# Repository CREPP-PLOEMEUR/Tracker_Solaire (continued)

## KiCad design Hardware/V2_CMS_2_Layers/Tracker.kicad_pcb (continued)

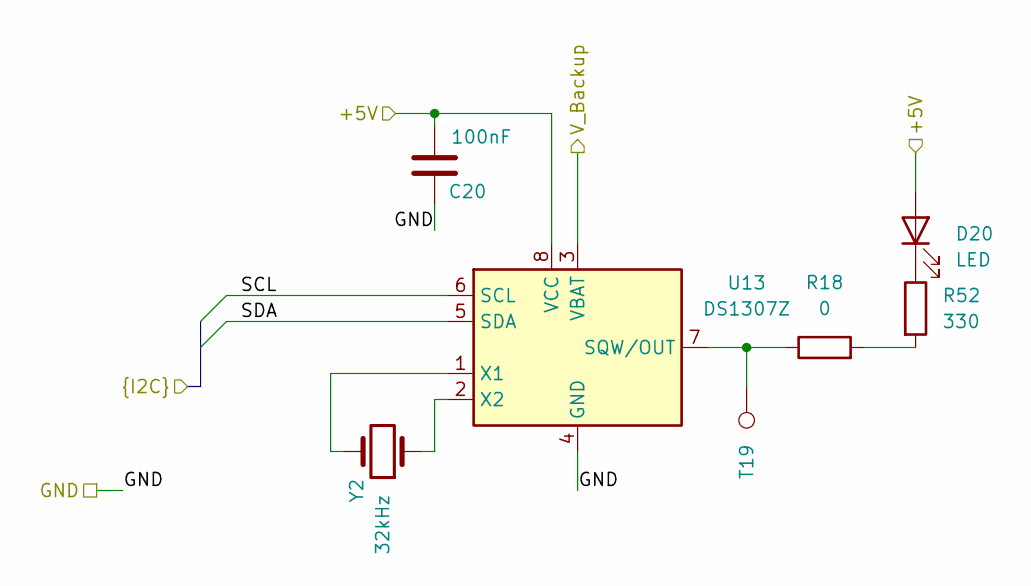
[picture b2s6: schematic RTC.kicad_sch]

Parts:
C20: 100nF; C_0603_1608Metric
D20: LED; LED_0603_1608Metric
R18: 0; R_0603_1608Metric
R52: 330; R_0603_1608Metric
T19: TP; TestPoint_Pad_D1.0mm
U13: DS1307Z; SO-8_5.3x6.2mm_P1.27mm
Y2: 32kHz; Crystal_SMD_3215-2Pin_3.2x1.5mm

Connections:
+VCap: U13.3 (VBAT); also elsewhere on the board
/Anemometer/SCL: U13.6 (SCL); also elsewhere on the board
unnamed: D20.1 (K), R52.1
unnamed: R18.2, R52.2
unnamed: R18.1, T19.1, U13.7 (SQW/OUT)
unnamed: U13.1 (X1), Y2.2
unnamed: U13.2 (X2), Y2.1

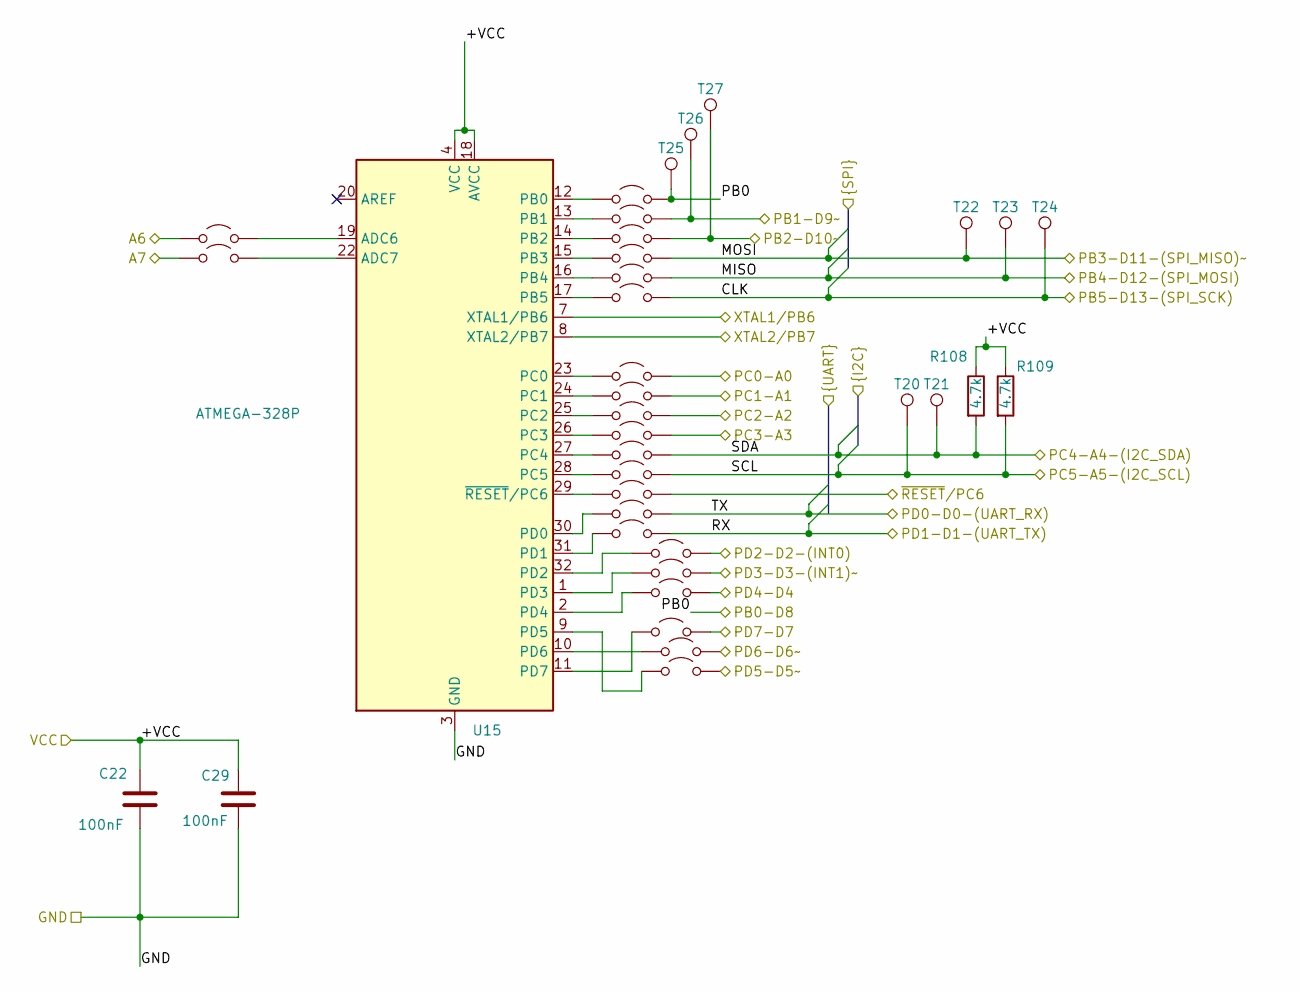
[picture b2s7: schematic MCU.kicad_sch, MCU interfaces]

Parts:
C22, C29: 100nF; C_0603_1608Metric
JP1, JP2, JP3, JP9, JP10, JP11, JP12, JP13, JP14, JP15, JP16, JP17, JP18, JP19, JP20, JP21, JP22, JP23, JP24, JP25, JP26, JP27, JP28: Jumper_2_Open; PinHeader_1x02_P1.27mm_Vertical
R108, R109: 4.7k; R_0603_1608Metric
T20, T21, T22, T23, T24, T25, T26, T27: TP; TestPoint_Pad_D1.0mm
U15: ATMEGA-328P; TQFP-32_7x7mm_P0.8mm

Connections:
/Anemometer/SCL: JP19.2 (B), R109.2, T20.1; also elsewhere on the board
/DTR: JP20.2 (B); also elsewhere on the board
/GNSS_RX: JP27.2 (B); also elsewhere on the board
/GNSS_TX: JP26.2 (B); also elsewhere on the board
/MCU/A6: JP1.2 (B); also elsewhere on the board
/MCU/A7: JP3.2 (B); also elsewhere on the board
/MCU/CLK: JP13.2 (B), T24.1; also elsewhere on the board
/MCU/MISO: JP12.2 (B), T23.1; also elsewhere on the board
/MCU/MOSI: JP11.2 (B), T22.1; also elsewhere on the board
/MCU/PB0: JP2.2 (B), T25.1; also elsewhere on the board
/MCU/PB1-D9~: JP9.2 (B), T26.1; also elsewhere on the board
/MCU/PB2-D10~: JP10.2 (B), T27.1; also elsewhere on the board
/MCU/PC0-A0: JP14.2 (B); also elsewhere on the board
/MCU/PC2-A2: JP16.2 (B); also elsewhere on the board
/MCU/PC3-A3: JP17.2 (B); also elsewhere on the board
/MCU/PD3-D3-(INT1)~: JP24.2 (B); also elsewhere on the board
/MCU/PD4-D4: JP25.2 (B); also elsewhere on the board
/MCU/PD5-D5~: JP28.2 (B); also elsewhere on the board
/MCU/RX: JP22.2 (B); also elsewhere on the board
/MCU/TX: JP21.2 (B); also elsewhere on the board
/WIND_INTERRUPT: JP23.2 (B); also elsewhere on the board
unnamed: JP1.1 (A), U15.19 (ADC6)
unnamed: JP2.1 (A), U15.12 (PB0)
unnamed: JP3.1 (A), U15.22 (ADC7)
unnamed: JP9.1 (A), U15.13 (PB1)
unnamed: JP10.1 (A), U15.14 (PB2)
unnamed: JP11.1 (A), U15.15 (PB3)
unnamed: JP12.1 (A), U15.16 (PB4)
unnamed: JP13.1 (A), U15.17 (PB5)
unnamed: JP14.1 (A), U15.23 (PC0)
unnamed: JP15.1 (A), U15.24 (PC1)
unnamed: JP16.1 (A), U15.25 (PC2)
unnamed: JP17.1 (A), U15.26 (PC3)
unnamed: JP18.1 (A), U15.27 (PC4)
unnamed: JP19.1 (A), U15.28 (PC5)
unnamed: JP20.1 (A), U15.29 (~RESET/PC6)
unnamed: JP21.1 (A), U15.30 (PD0)
unnamed: JP22.1 (A), U15.31 (PD1)
unnamed: JP23.1 (A), U15.32 (PD2)
unnamed: JP24.1 (A), U15.1 (PD3)
unnamed: JP25.1 (A), U15.2 (PD4)
unnamed: JP26.1 (A), U15.11 (PD7)
unnamed: JP27.1 (A), U15.10 (PD6)
unnamed: JP28.1 (A), U15.9 (PD5)

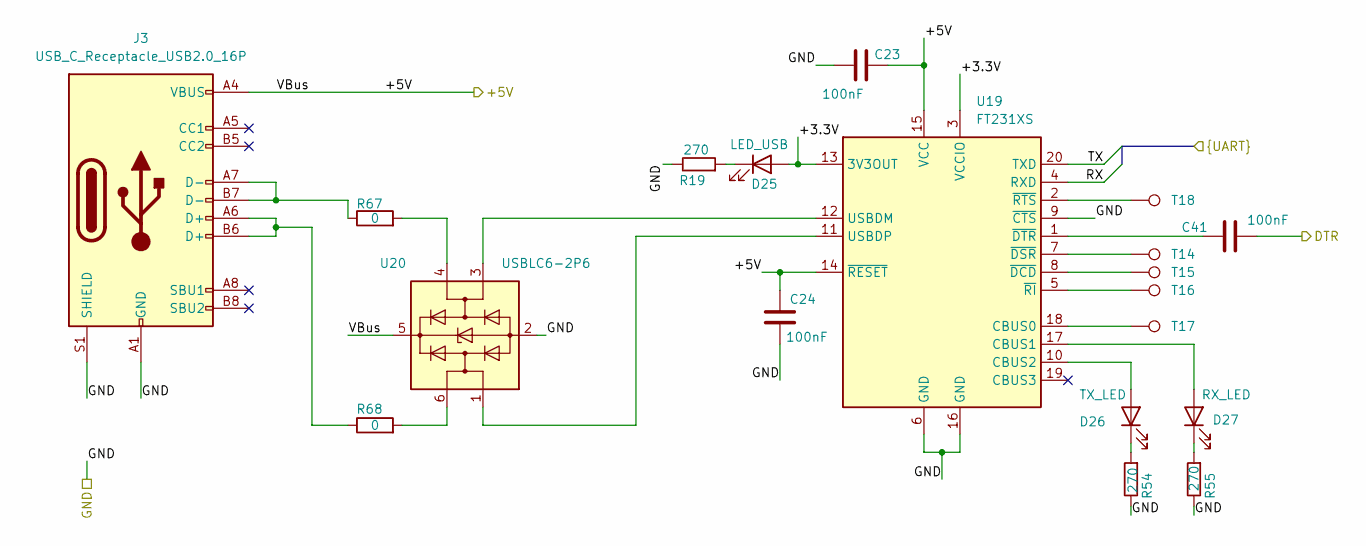
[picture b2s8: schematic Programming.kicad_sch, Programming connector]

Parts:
C23, C24, C41: 100nF; C_0603_1608Metric
D25: LED_USB; LED_0603_1608Metric
D26: TX_LED; LED_0603_1608Metric
D27: RX_LED; LED_0603_1608Metric
J3: USB_C_Receptacle_USB2.0_16P; USB_C_Receptacle_GCT_USB4085
R19, R54, R55: 270; R_0603_1608Metric
R67, R68: 0; R_0603_1608Metric
T14, T15, T16, T17, T18: TP; TestPoint_Pad_D1.0mm
U19: FT231XS; SSOP-20_3.9x8.7mm_P0.635mm
U20: USBLC6-2P6; SOT-666

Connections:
/DTR: C41.2; also elsewhere on the board
/MCU/RX: U19.4 (RXD); also elsewhere on the board
/MCU/TX: U19.20 (TXD); also elsewhere on the board
/Programming/+3.3V: D25.2 (A), U19.3 (VCCIO), U19.13 (3V3OUT)
unnamed: D25.1 (K), R19.1
unnamed: D26.2 (A), U19.10 (CBUS2)
unnamed: D26.1 (K), R54.1
unnamed: D27.2 (A), U19.17 (CBUS1)
unnamed: D27.1 (K), R55.1
unnamed: J3.A6 (D+), J3.B6 (D+), R68.1
unnamed: J3.A7 (D-), J3.B7 (D-), R67.1
unnamed: R67.2, U20.4 (I/O2)
unnamed: R68.2, U20.6 (I/O1)
unnamed: T17.1, U19.18 (CBUS0)
unnamed: U19.12 (USBDM), U20.3 (I/O2)
unnamed: U19.11 (USBDP), U20.1 (I/O1)
unnamed: T15.1, U19.8 (~DCD)
unnamed: T14.1, U19.7 (~DSR)
unnamed: C41.1, U19.1 (~DTR)
unnamed: T16.1, U19.5 (~RI)
unnamed: T18.1, U19.2 (~RTS)

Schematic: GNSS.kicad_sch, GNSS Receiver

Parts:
AE1: Internal_antenna; MountingHole_2.2mm_M2_DIN965_Pad
C7, C36: 100nF; C_0603_1608Metric
C9, C10, C34: 120pF; C_0603_1608Metric
C25, C26: 330pF; C_0603_1608Metric
C35: 1nF; C_0603_1608Metric
D2: POS_ENABLE; LED_0603_1608Metric
D24: GNSS_USB; LED_0603_1608Metric
D28: LED_EXT_ANTENNA; LED_0603_1608Metric
D34: GNSS_BATT; LED_0603_1608Metric
D36: 1N4148; D_SOD-323
J5: USB_C_Receptacle_USB2.0_16P; USB_C_Receptacle_GCT_USB4085
J10: 132415; SMA_Molex_73251-1153_EdgeMount_Horizontal
L6: 56nH; L_0603_1608Metric
L9: 39nH; L_0603_1608Metric
Q1: SI2302; SOT-23
Q10: CJ3401; SOT-23
Q11: 2N7002; SOT-23
R11, R12, R15, R69, R70, R71, R72, R94, R106, R107: 0; R_0603_1608Metric
R13, R14, R58: 1k; R_0603_1608Metric
R16, R73, R74, R95: 330; R_0603_1608Metric
R17: R_680K_SMD_0603; R_0603_1608Metric
R56: 100k; R_0603_1608Metric
R57: 10k; R_0603_1608Metric
R92: R_100K_SMD_0603; R_0603_1608Metric
R93: R_1K_SMD_0603; R_0603_1608Metric
T1, T4, T5, T7, T8, T33, T34, T38, T40, T52: TP; TestPoint_Pad_D1.0mm
U3: NEO-M8M; ublox_NEO
U21: AS193-73LF; SOT-23-6
U26: USBLC6-2P6; SOT-666
U27: LP2985-3.3; SOT-23-5

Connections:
+VCap_GNSS: U3.22 (V_BCKP); also elsewhere on the board
/GNSS/D+: U3.6 (USB_DP), U26.3 (I/O2)
/GNSS/D-: U3.5 (USB_DM), U26.1 (I/O1)
/GNSS/VBus: J5.A4 (VBUS), J5.A9 (VBUS), J5.B4 (VBUS), J5.B9 (VBUS), R71.1, U26.5 (VBUS)
/GNSS/VCC_RF: L9.2, R17.2, U3.9 (VCC_RF)
/GNSS/VCC_USB: C36.1, D36.2 (A), R72.2, U3.7 (VDD_USB), U27.5 (VOUT)
/GNSS/~ANTENNA_DETECT: C26.1, L6.1, Q1.1 (G), R17.1, R57.2, T52.1, U21.6 (V1)
/GNSS_ENABLED: R107.2; also elsewhere on the board
/GNSS_RX: R12.1; also elsewhere on the board
/GNSS_TX: R11.1; also elsewhere on the board
unnamed: AE1.1 (A), C10.2
unnamed: C25.2, L6.2, R56.2
unnamed: D2.2 (A), R16.1
unnamed: D24.2 (A), R73.1
unnamed: D28.1 (K), R74.2
unnamed: D34.2 (A), R95.1
unnamed: D36.1 (K), Q11.1 (G), R92.2, R107.1
unnamed: J5.A6 (D+), J5.B6 (D+), R69.1
unnamed: J5.A7 (D-), J5.B7 (D-), R70.1
unnamed: C34.2, J10.1 (In), L9.1, R56.1
unnamed: Q1.2 (S), R58.2, R106.2, T1.1, U21.4 (V2)
unnamed: Q10.3 (D), R94.2, T40.1, U3.23 (VCC)
unnamed: Q10.1 (G), Q11.3 (D), R93.1
unnamed: R12.2, R13.1
unnamed: R15.1, R16.2
unnamed: R69.2, U26.4 (I/O2)
unnamed: R70.2, U26.6 (I/O1)
unnamed: R72.1, R73.2
unnamed: R94.1, R95.2
unnamed: R74.1, R106.1
unnamed: T38.1, U3.2 (D_SEL)
unnamed: T8.1, U3.4 (EXTINT)
unnamed: C9.2, U3.11 (RF_IN)
unnamed: R13.2, R14.2, T4.1, U3.21 (RXD/SPI_MOSI)
unnamed: T34.1, U3.19 (SCL/SPI_CLK)
unnamed: T33.1, U3.18 (SDA/~SPI_CS)
unnamed: R15.2, U3.3 (TIMEPULSE)
unnamed: R11.2, T5.1, U3.20 (TXD/SPI_MISO)
unnamed: T7.1, U3.1 (~SAFEBOOT)
unnamed: C9.1, U21.5 (J1)
unnamed: C10.1, U21.1 (J2)
unnamed: C34.1, U21.3 (J3)
unnamed: C35.1, U27.4 (BP)
unnamed: R71.2, U27.1 (VIN), U27.3 (ON/~OFF)

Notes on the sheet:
V_{RX}=5*${a52a78e2-18e3-4ec6-8d46-591b24bd5bd1:VALUE}/(${a52a78e2-18e3-4ec6-8d46-591b24bd5bd1:VALUE}+${f5d83104-4b79-4b80-ade9-bfd7c6659042:VALUE})
EXT_ANTENNA

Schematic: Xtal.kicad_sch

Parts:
C7, C8: 22pF; C_Disc_D4.7mm_W2.5mm_P5.00mm
Y1: 16MHz; Crystal_HC49-4H_Vertical

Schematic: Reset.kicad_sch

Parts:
J11: KF128-2.54_2P; TerminalBlock_Phoenix_MPT-0,5-2-2.54_1x02_P2.54mm_Horizontal
R46: 10k; R_0603_1608Metric
SW4: PB_SMD_12V_50MA_6MM_6MM; SW_Push_1P1T_NO_CK_KSC7xxJ

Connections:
/DTR: J11.2, R46.2, SW4.2 (B); also elsewhere on the board

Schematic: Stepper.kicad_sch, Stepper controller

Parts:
C30: 100nF; C_0603_1608Metric
C31, C32: XX; C_0603_1608Metric
D22, D35: 1N4148; D_SOD-323
IC1: L6208; ST_PowerSSO-36_SlugDown_ThermalVias
J16: Stepper; PhoenixContact_MSTBA_2,5_4-G-5,08_1x04_P5.08mm_Horizontal
J22: KF128-2.54_2P; TerminalBlock_Phoenix_MPT-0,5-2-2.54_1x02_P2.54mm_Horizontal
J26: +24V; PhoenixContact_MSTBA_2,5_2-G-5,08_1x02_P5.08mm_Horizontal
J31: Motor_Control_Pull_Up; TerminalBlock_Phoenix_MPT-0,5-3-2.54_1x03_P2.54mm_Horizontal
J32: KF128-2.54_3P; TerminalBlock_Phoenix_MPT-0,5-3-2.54_1x03_P2.54mm_Horizontal
R64, R97, R99, R101: 10k; R_0603_1608Metric
R65, R66: XX; R_0603_1608Metric
R79, R80: 0.33; R_Axial_DIN0414_L11.9mm_D4.5mm_P15.24mm_Horizontal
R84, R85, R86, R87, R88, R89: 220; R_0603_1608Metric
R98, R100: 10k; R_0603_1608Metric; not fitted
R103: 0; R_0603_1608Metric
RV2: Vref_B; Potentiometer_Bourns_3314S_Horizontal
RV3: Vref_A; Potentiometer_Bourns_3314S_Horizontal
T3, T28, T29, T30, T31, T32, T42: TP; TestPoint_Pad_D1.0mm
U23, U24, U25: PC817XI; SOP-4_4.4x2.6mm_P1.27mm

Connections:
+24V: D35.2 (A), IC1.17 (VS_B), IC1.20 (VS_A), J26.2; also elsewhere on the board
/MCU/A7: J22.2, R64.2; also elsewhere on the board
/MCU/PB0: U24.2; also elsewhere on the board
/MCU/PB1-D9~: U25.2; also elsewhere on the board
/MCU/PB2-D10~: U23.2; also elsewhere on the board
/Stepper/CONTROL: IC1.13 (CONTROL), R97.2, R98.1, T42.1
/Stepper/HALF/FULL: IC1.12 (HALF/FULL), R99.2, R100.1, T3.1
/Stepper/RC_1: C31.1, IC1.4 (RCA), R65.2, T28.1
/Stepper/RC_2: C32.1, IC1.9 (RCB), R66.2, T29.1
/Stepper/SENSE_A: IC1.3 (SENSE_A), R80.1
/Stepper/SENSE_B: IC1.10 (SENSE_B), R79.1
/Stepper/STEP_CW: IC1.2 (CW/CWW), J32.1, R88.2, T31.1, U24.4
/Stepper/STEP_ENABLE: IC1.14 (EN), J32.2, R87.2, T32.1, U25.4
/Stepper/STEP_PULSE: IC1.1 (CLOCK), J32.3, R89.2, T30.1, U23.4
/Stepper/Vref_A: IC1.24 (VREF_A), RV3.2
/Stepper/Vref_B: IC1.11 (VREF_B), RV2.2
unnamed: C30.2, R101.2
unnamed: C30.1, D22.2 (A), D35.1 (K)
unnamed: D22.1 (K), IC1.15 (VBOOT)
unnamed: IC1.5 (OUT1A), J16.1
unnamed: IC1.8 (OUT1B), J16.3
unnamed: IC1.21 (OUT2A), J16.2
unnamed: IC1.16 (OUT2B), J16.4
unnamed: IC1.22 (VCP), R101.1
unnamed: R84.1, U23.1
unnamed: R85.1, U24.1
unnamed: R86.1, U25.1
unnamed: R64.1, R103.1

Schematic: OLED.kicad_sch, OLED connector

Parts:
J8: I2C_Selector; PinHeader_2x03_P2.54mm_Vertical
J9: OLED_SOCKET; PinSocket_1x04_P2.54mm_Vertical

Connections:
/Anemometer/SCL: J8.5, J8.6; also elsewhere on the board
/OLED/A: J8.4, J9.1
/OLED/B: J8.3, J9.2

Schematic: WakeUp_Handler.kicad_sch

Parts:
D30, D32: 1N4148; D_SOD-323
J35, J36: KF128-2.54_2P; TerminalBlock_Phoenix_MPT-0,5-2-2.54_1x02_P2.54mm_Horizontal
Q9: 2N7002; SOT-23
R75, R76, R81, R82, R83: 10k; R_0603_1608Metric
RV1: Light_Reference; Potentiometer_Bourns_3314S_Horizontal
SW7: PB_SMD_12V_50MA_6MM_6MM; SW_Push_1P1T_NO_CK_KSC7xxJ
T35, T36, T44, T50, T51: TP; TestPoint_Pad_D1.0mm
U29: LM358DR; TSSOP-8_4.4x3mm_P0.65mm

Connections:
/Power_Supply/WakeUp_Handler/PS_CTRL: Q9.3 (D), R76.1, T36.1; also elsewhere on the board
/Power_Supply/WakeUp_Handler/WIND_INTERRUPT: D30.2 (A); also elsewhere on the board
unnamed: D30.1 (K), D32.1 (K), Q9.1 (G), R82.2, R83.2, T50.1, U29.1
unnamed: D32.2 (A), J36.2, SW7.1 (A), T51.1
unnamed: J35.1, R75.2, R81.1, T35.1
unnamed: R81.2, R82.1, U29.3 (+)
unnamed: RV1.2, T44.1, U29.2 (-)

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
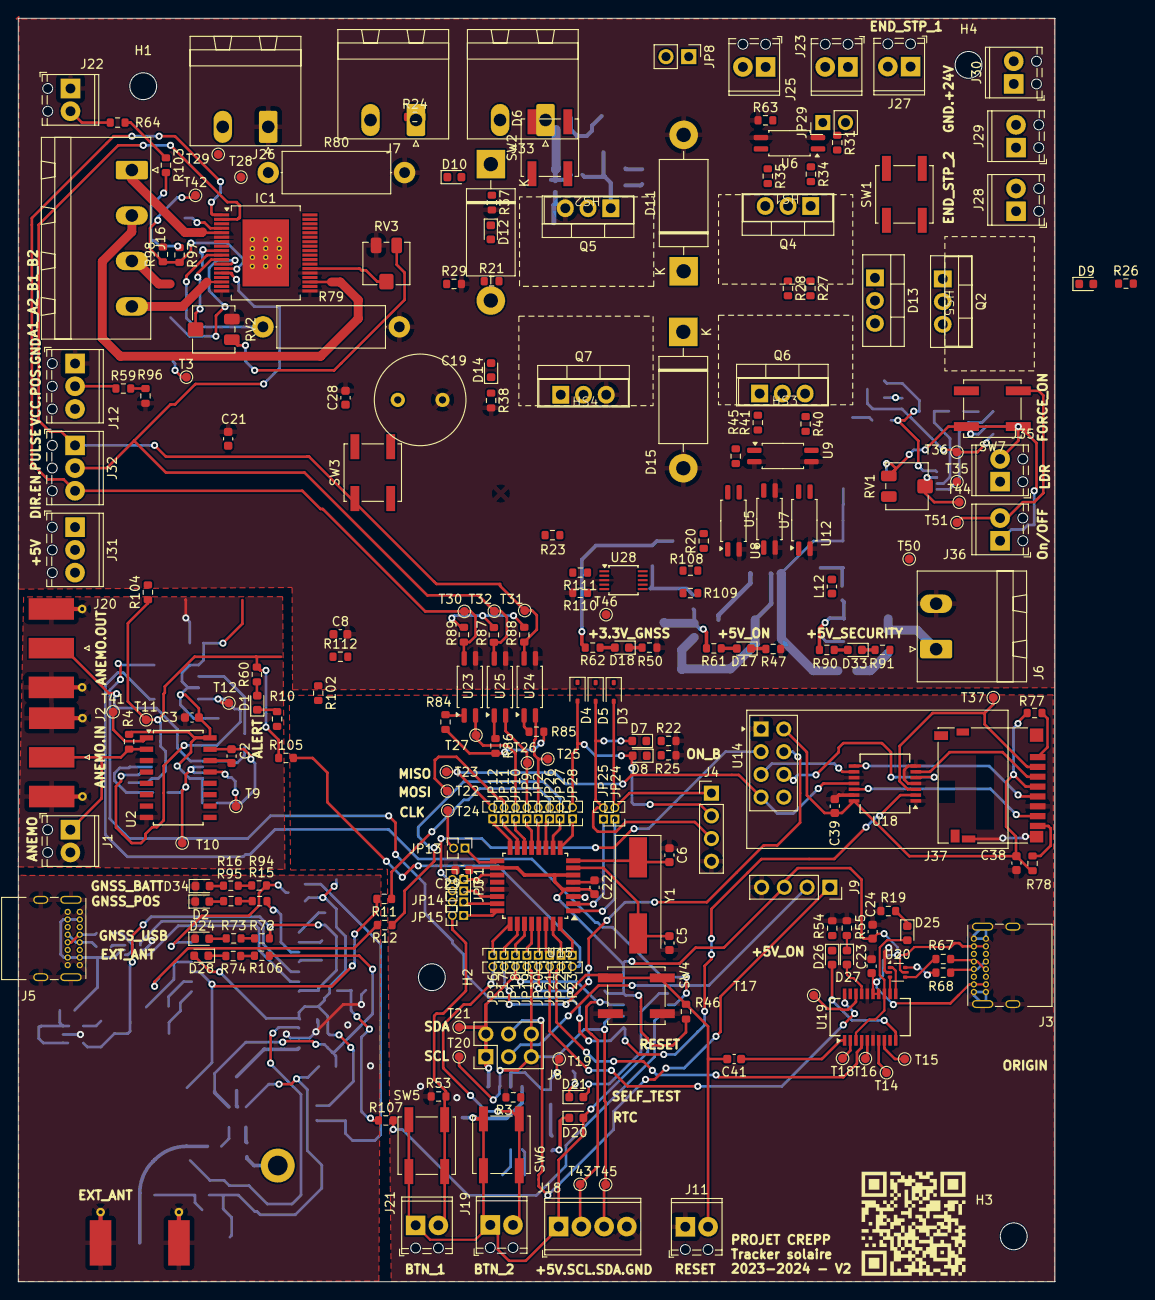
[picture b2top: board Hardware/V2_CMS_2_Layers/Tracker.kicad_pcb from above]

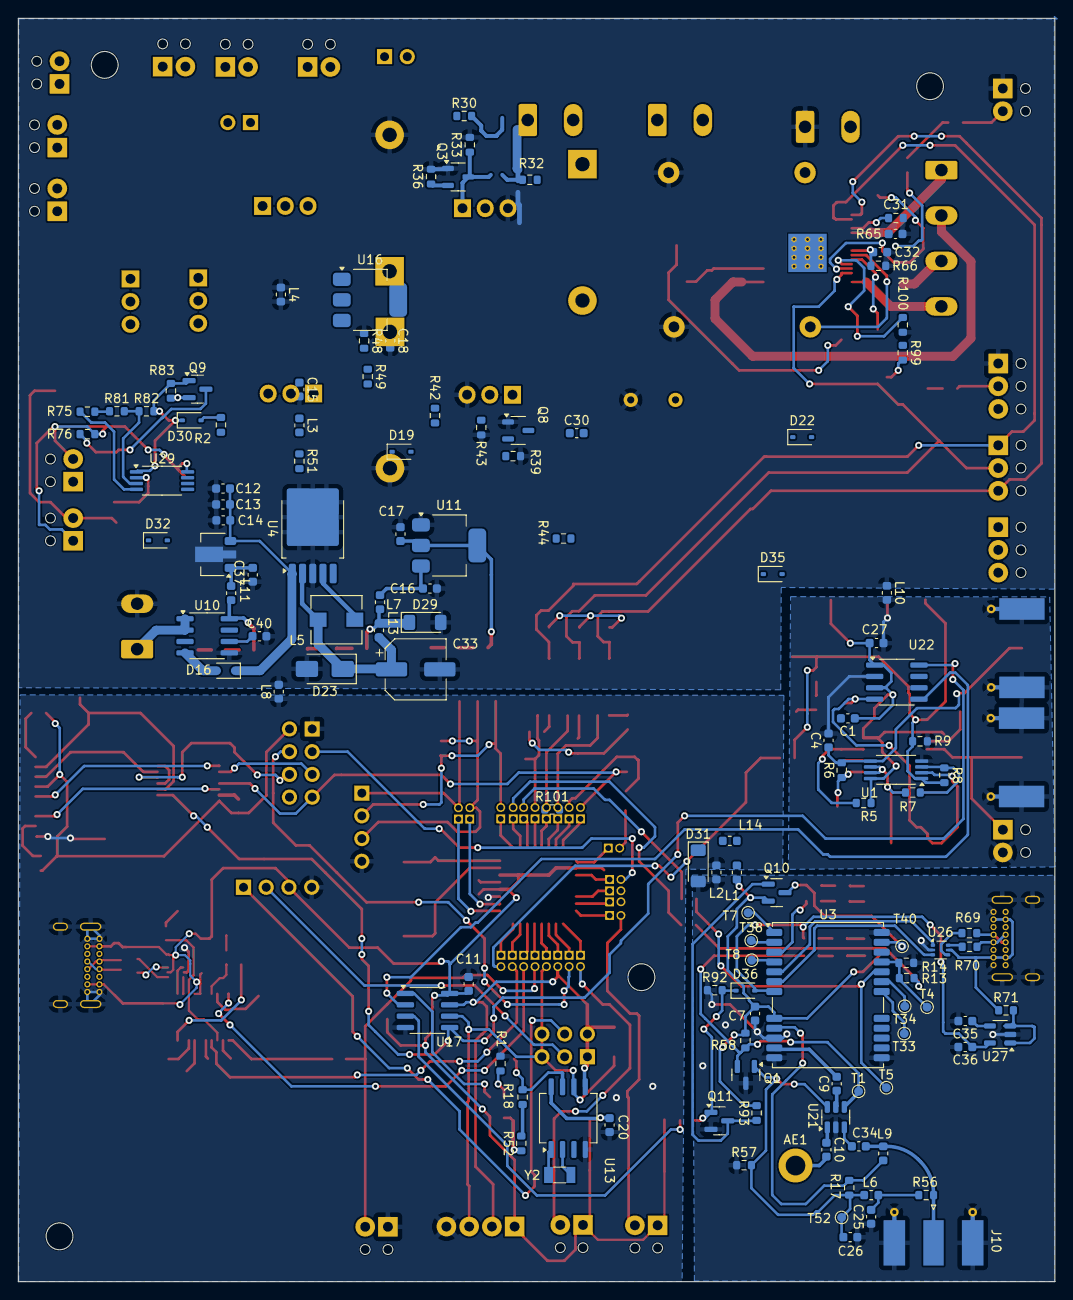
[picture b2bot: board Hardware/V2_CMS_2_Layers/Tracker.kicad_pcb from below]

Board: 2 copper layers, 115.8 x 141.2 mm, 367 parts (123 on the bottom side), 235 nets.

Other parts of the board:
C5, C6: 22pF; C_0603_1608Metric
C11, C21, C38, C39: 100nF; C_0603_1608Metric
C28: 4.7u; C_0603_1608Metric
D21: LED; LED_0603_1608Metric
J18: KF128-2.54_4P; TerminalBlock_Phoenix_MPT-0,5-4-2.54_1x04_P2.54mm_Horizontal
J19, J21: KF128-2.54_2P; TerminalBlock_Phoenix_MPT-0,5-2-2.54_1x02_P2.54mm_Horizontal
J37: Micro_SD_Card; microSD_HC_Hirose_DM3D-SF
R1: 330; R_0603_1608Metric
R3, R53, R77, R78, R110, R111: 10k; R_0603_1608Metric
SW6: SW_User; SW_Push_1P1T_NO_CK_KSC7xxJ
T37, T43, T45, T46: TP; TestPoint_Pad_D1.0mm
U14: NRF24L01_Breakout; nRF24L01_Breakout
U17: PCA9536D; SOIC-8_3.9x4.9mm_P1.27mm
U18: LVC125A; SSOP-14_5.3x6.2mm_P0.65mm
U28: ADS1115IDGS; TSSOP-10_3x3mm_P0.5mm

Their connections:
+3.3V: C21.1, C28.1, C38.1, C39.1, J37.4 (VDD), R77.2, R78.2, U14.2 (VCC), U18.14 (VCC); also elsewhere on the board
/Anemometer/SCL: J18.3, T45.1, U17.6 (SCL), U28.9 (SDA); also elsewhere on the board
/CLK_POT_NUM/~CS_SD: U17.5 (IO3), U18.2; also elsewhere on the board
/GNSS_ENABLED: U17.3 (IO2); also elsewhere on the board
/IO_Extender/+5V_Security: R111.1, U28.8 (VDD)
/MCU/A6: U14.3 (CE); also elsewhere on the board
/MCU/CLK: U14.5 (SCK), U18.9; also elsewhere on the board
/MCU/MISO: U14.7 (MISO), U18.11; also elsewhere on the board
/MCU/MOSI: U14.6 (MOSI), U18.5; also elsewhere on the board
/MCU/PC2-A2: J19.2, R3.1, SW6.2 (B); also elsewhere on the board
/MCU/PC3-A3: U14.4 (~CSN); also elsewhere on the board
/SD_Reader/VoltageTranslator/1Y: J37.2 (DAT3/CD), T37.1, U18.3
/SD_Reader/VoltageTranslator/2Y: J37.3 (CMD), U18.6
/SD_Reader/VoltageTranslator/3Y: J37.5 (CLK), U18.8
/SD_Reader/VoltageTranslator/4A: J37.7 (DAT0), U18.12
/SIMULATE_WIND/~CS_NUM_POT: U17.2 (IO1); also elsewhere on the board
unnamed: D21.2 (A), U17.1 (IO0)
unnamed: D21.1 (K), R1.1
unnamed: J37.8 (DAT1), R78.1
unnamed: J37.1 (DAT2), R77.1
unnamed: R110.1, R111.2, U28.1 (ADDR)
unnamed: T46.1, U28.2 (ALERT/RDY)

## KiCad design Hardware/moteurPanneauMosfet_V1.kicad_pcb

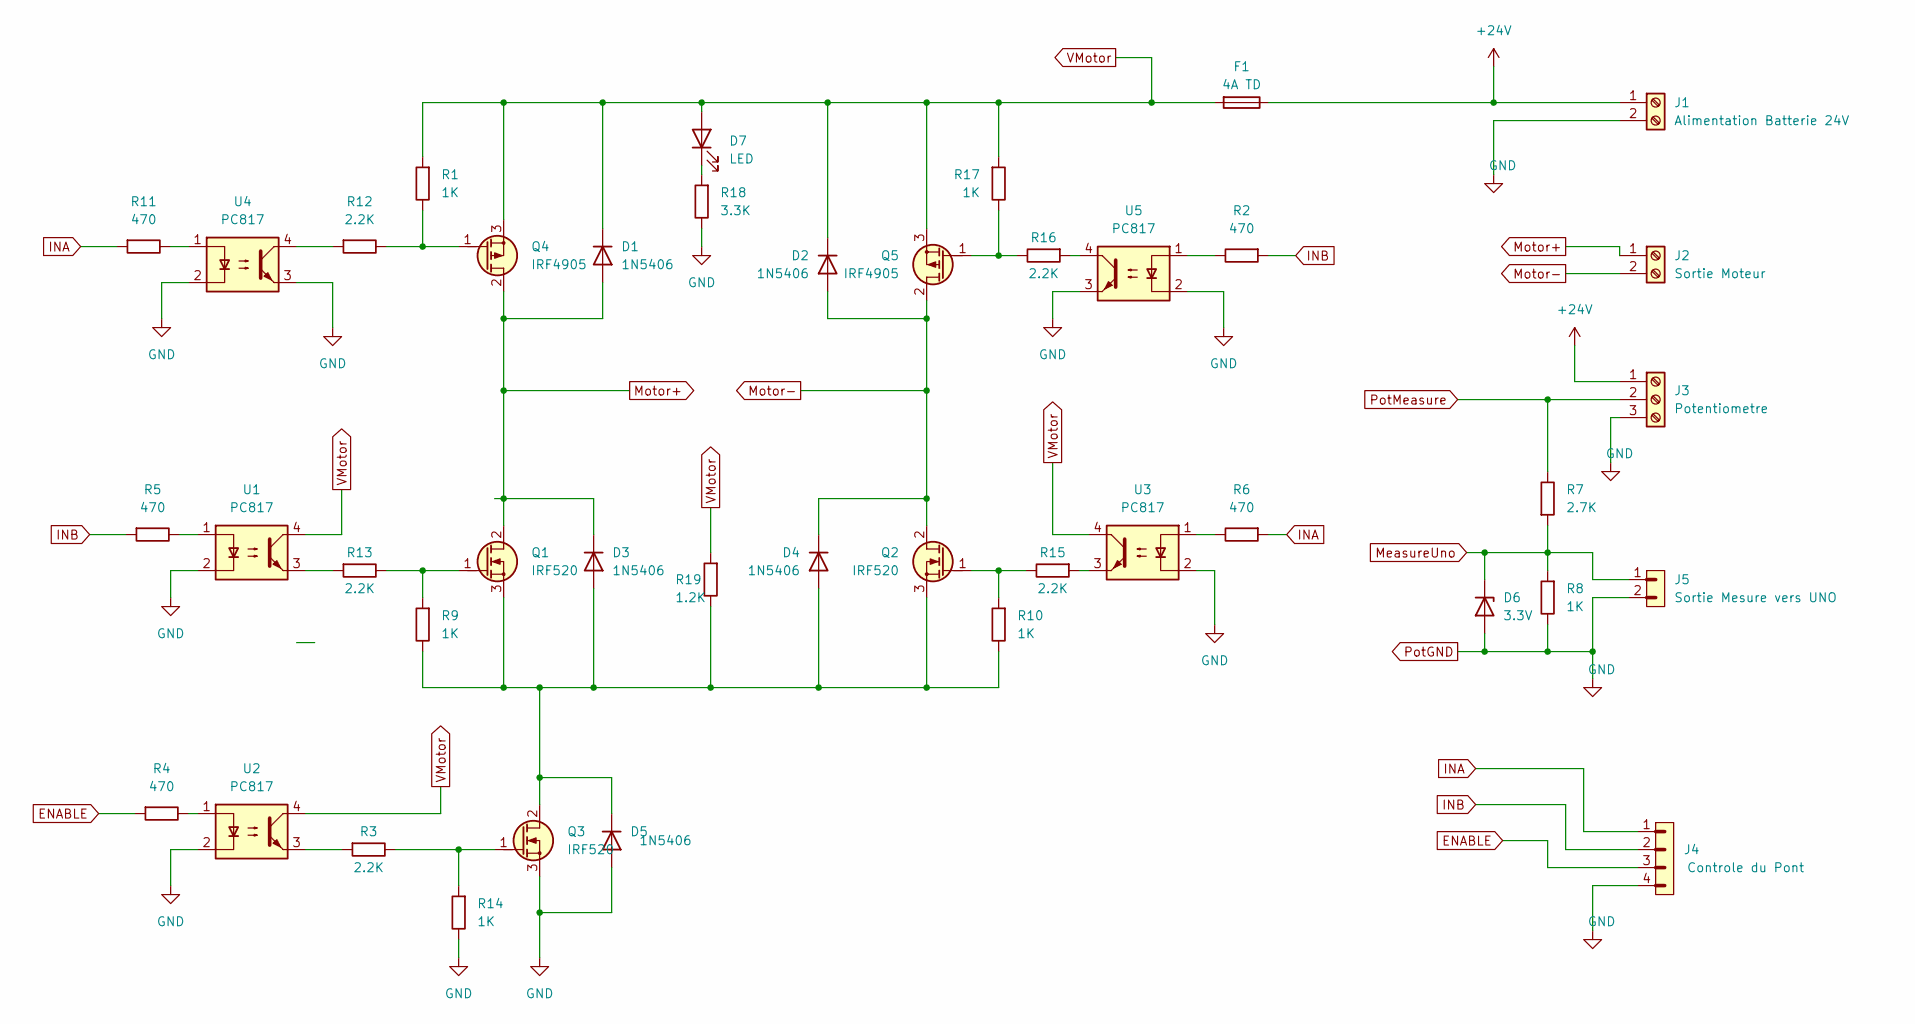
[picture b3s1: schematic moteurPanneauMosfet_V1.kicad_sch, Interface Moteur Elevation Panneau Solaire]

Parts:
D1, D2, D3, D4, D5: 1N5406; D_DO-201AD_P15.24mm_Horizontal
D6: 3.3V; D_A-405_P10.16mm_Horizontal
D7: LED; LED_D3.0mm
F1: 4A TD; Fuseholder_Cylinder-5x20mm_Schurter_OGN-SMD_Horizontal_Open
J1: Alimentation Batterie 24V; TerminalBlock_Phoenix_MKDS-1,5-2-5.08_1x02_P5.08mm_Horizont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
J2: Sortie Moteur; TerminalBlock_Phoenix_MKDS-1,5-2-5.08_1x02_P5.08mm_Horizont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
J3: Potentiometre; TerminalBlock_Phoenix_MKDS-1,5-3-5.08_1x03_P5.08mm_Horizont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
J4: Controle du Pont; PinHeader_1x04_P2.54mm_Vertical
J5: Sortie Mesure vers UNO; PinHeader_1x02_P2.54mm_Vertical
Q1, Q2, Q3: IRF520; TO-220-3_Vertical
Q4, Q5: IRF4905; TO-220-3_Vertical
R1, R9, R10, R14, R17: 1K; R_Axial_DIN0309_L9.0mm_D3.2mm_P15.24mm_Horizontal
R2, R4, R5, R6, R11: 470; R_Axial_DIN0309_L9.0mm_D3.2mm_P15.24mm_Horizontal
R3, R12, R13, R15, R16: 2.2K; R_Axial_DIN0309_L9.0mm_D3.2mm_P15.24mm_Horizontal
R7: 2.7K; R_Axial_DIN0207_L6.3mm_D2.5mm_P10.16mm_Horizontal
R8: 1K; R_Axial_DIN0207_L6.3mm_D2.5mm_P10.16mm_Horizontal
R18: 3.3K; R_Axial_DIN0309_L9.0mm_D3.2mm_P15.24mm_Horizontal
R19: 1.2K; R_Axial_DIN0516_L15.5mm_D5.0mm_P20.32mm_Horizontal
U1, U2, U3, U4, U5: PC817; DIP-4_W7.62mm

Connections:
+24V: F1.1, J1.1, J3.1
ENABLE: J4.3, R4.1
INA: J4.1, R6.1, R11.1
INB: J4.2, R2.1, R5.1
MeasureUno: D6.1 (K), J5.1, R7.1, R8.1
Motor+: D1.2 (A), D3.1 (K), J2.1, Q1.2 (D), Q4.2 (D)
Motor-: D2.2 (A), D4.1 (K), J2.2, Q2.2 (D), Q5.2 (D)
unnamed: D3.2 (A), D4.2 (A), D5.1 (K), Q1.3 (S), Q2.3 (S), Q3.2 (D), R9.2, R10.2, R19.2
unnamed: D7.1 (K), R18.1
unnamed: Q1.1 (G), R9.1, R13.2
unnamed: Q2.1 (G), R10.1, R15.2
unnamed: Q3.1 (G), R3.2, R14.1
unnamed: Q4.1 (G), R1.2, R12.2
unnamed: Q5.1 (G), R16.2, R17.2
unnamed: R2.2, U5.1
unnamed: R3.1, U2.3
unnamed: R4.2, U2.1
unnamed: R5.2, U1.1
unnamed: R6.2, U3.1
unnamed: R11.2, U4.1
unnamed: R12.1, U4.4
unnamed: R13.1, U1.3
unnamed: R15.1, U3.3
unnamed: R16.1, U5.4
PotGND: D5.2 (A), D6.2 (A), J1.2, J3.3, J4.4, J5.2, Q3.3 (S), R8.2, R14.2, R18.2, U1.2, U2.2, U3.2, U4.2, U4.3, U5.2, U5.3
PotMeasure: J3.2, R7.2
VMotor: D1.1 (K), D2.1 (K), D7.2 (A), F1.2, Q4.3 (S), Q5.3 (S), R1.1, R17.1, R19.1, U1.4, U2.4, U3.4

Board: 2 copper layers, 42 parts (0 on the bottom side), 27 nets, no tracks yet.

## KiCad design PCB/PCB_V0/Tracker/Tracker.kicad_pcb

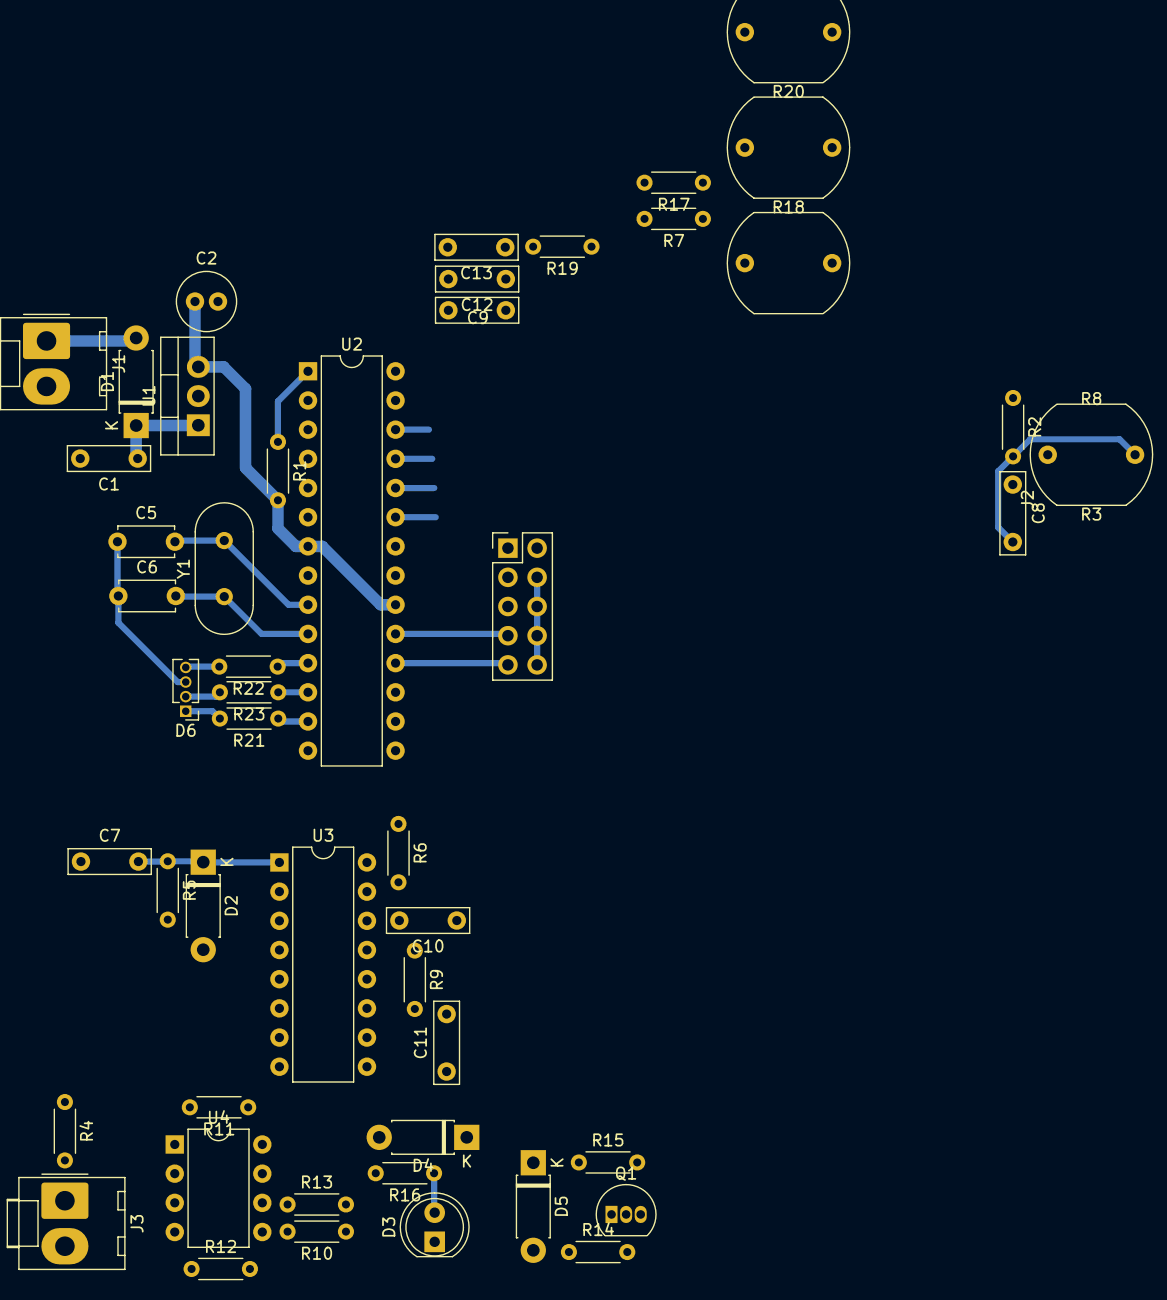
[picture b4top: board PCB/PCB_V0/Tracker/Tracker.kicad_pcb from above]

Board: 2 copper layers, 49 parts (0 on the bottom side), 34 nets.

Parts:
C1, C7, C10, C11: 1nF; C_Rect_L7.0mm_W2.0mm_P5.00mm
C2: 4.7uF; C_Radial_D5.0mm_H11.0mm_P2.00mm
C5, C6: 22pF; C_Disc_D4.7mm_W2.5mm_P5.00mm
C8, C9, C12, C13: 100nF; C_Rect_L7.0mm_W2.0mm_P5.00mm
D1, D2, D4, D5: 1N4818; D_DO-41_SOD81_P7.62mm_Horizontal
D3: LED; LED_D5.0mm
D6: LED_RBKG; PinHeader_1x04_P1.27mm_Vertical
J1: Battery; Molex_KK-396_A-41791-0002_1x02_P3.96mm_Vertical
J2: SPI_Programming; PinHeader_2x05_P2.54mm_Vertical
J3: Wind; Molex_KK-396_A-41791-0002_1x02_P3.96mm_Vertical
Q1: BC337; TO-92_Inline
R1, R9, R10, R11, R13, R14, R15, R16: 10k; R_Axial_DIN0204_L3.6mm_D1.6mm_P5.08mm_Horizontal
R2, R6, R7, R17, R19: 100k; R_Axial_DIN0204_L3.6mm_D1.6mm_P5.08mm_Horizontal
R3, R8, R18, R20: LDR03; R_LDR_10x8.5mm_P7.6mm_Vertical
R4: 470k; R_Axial_DIN0204_L3.6mm_D1.6mm_P5.08mm_Horizontal
R5: 270k; R_Axial_DIN0204_L3.6mm_D1.6mm_P5.08mm_Horizontal
R12: 47k; R_Axial_DIN0204_L3.6mm_D1.6mm_P5.08mm_Horizontal
R21, R22, R23: 270; R_Axial_DIN0204_L3.6mm_D1.6mm_P5.08mm_Horizontal
U1: L7805; TO-220-3_Vertical
U2: ATmega328P-P; DIP-28_W7.62mm
U3: 74HC123; DIP-16_W7.62mm
U4: TL082; DIP-8_W7.62mm
Y1: 16MHz; Crystal_HC49-4H_Vertical

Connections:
+5V: C2.1, J2.2, R1.2, R2.1, R4.1, R6.1, R7.1, R11.1, R15.2, R17.1, R19.1, U1.3 (OUT), U2.7 (VCC), U2.20 (AVCC), U3.16 (VCC), U4.8 (V+)
/MISO: J2.9, U2.18 (PB4)
/MOSI: J2.1, U2.17 (PB3)
/RST: J2.5, R1.1, U2.1 (~RESET/PC6)
/SCK: J2.7, U2.19 (PB5)
/SUN/LDR1: C8.2, R2.2, R3.1, U2.23 (PC0)
/SUN/LDR2: C9.2, R7.2, R8.1, U2.24 (PC1)
/SUN/LDR3: C12.2, R17.2, R18.1, U2.25 (PC2)
/SUN/LDR4: C13.2, R19.2, R20.1, U2.26 (PC3)
/WIND/OUT: D4.1 (K), D5.1 (K), U2.4 (PD2)
/WIND/SECURITY: R14.1, U2.5 (PD3)
/XTAL1: C5.2, U2.9 (XTAL1/PB6), Y1.2
/XTAL2: C6.2, U2.10 (XTAL2/PB7), Y1.1
GND: C1.2, C2.2, C5.1, C6.1, C8.1, C9.1, C10.1, C11.1, C12.1, C13.1, D2.2 (A), D3.1 (K), D6.3 (K), J1.2, J2.4, J2.6, J2.8, J2.10, J3.2, Q1.3 (E), R3.2, R5.2, R8.2, R12.1, R18.2, R20.2, U1.2 (GND), U2.8 (GND), U2.22 (GND), U3.8 (GND), U4.4 (V-)
unnamed: C11.2, R9.2, R10.1
unnamed: D1.2 (A), J1.1
unnamed: C1.1, D1.1 (K), U1.1 (IN)
unnamed: C7.2, D2.1 (K), R5.1, U3.1 (A)
unnamed: D3.2 (A), R16.1
unnamed: D4.2 (A), R13.2, R16.2, U4.7
unnamed: D5.2 (A), Q1.1 (C), R15.1
unnamed: D6.2 (BA), R23.2
unnamed: D6.4 (GA), R22.2
unnamed: D6.1 (RA), R21.2
unnamed: J3.1, R4.2, U4.3 (+)
unnamed: Q1.2 (B), R14.2
unnamed: R22.1, U2.11 (PD5)
unnamed: R23.1, U2.12 (PD6)
unnamed: R21.1, U2.13 (PD7)
unnamed: C10.2, R6.2, U3.14 (Cext), U3.15 (RCext)
unnamed: R9.1, U3.13 (Q)
unnamed: C7.1, U4.1, U4.2 (-)
unnamed: R10.2, R13.1, U4.5 (+)
unnamed: R11.2, R12.2, U4.6 (-)
